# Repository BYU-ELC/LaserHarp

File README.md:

# LaserHarp
Contains code and project files for the Laser Harp project

The Laser harp project accepts inputs from the laser sensors/beams. When a laser beam is interrupted, the consequent signal will be converted into a musical/audio output corresponding with the 'string' played. As such, this functions generally as a classical harp, simply implementing the lasers to operate as harp strings.

Currently the project is controlled by a teensy with an audio shield. The 5 volt power source is stepped down to 3.3 volts to power 8 always on lasers which are pointed at photodiodes. The photodiodes each have a simple BJT circuit to amplify their output which is detected by the teensy. The audio shield on the teensy generates a tone every time a laser beam is interrupted.

The original board schematic is handwritten in LaserHarpSchematic.pdf, but the new schematics and layouts are in the Laser Harp PCB.sch and Laser Harp PCB.brd files respectively. You should use these for future development or repair.

 --

FUTURE DEVELOPMENT:

Currently the Laser Harp is using a PCB we milled out here in the shop which is nice, but it might be nice to order a professional one. Also, it is Revision 2, meaning I had to manually change the connection from pin 7 to pin 8 (See schematic commit notes).

If the Photo Diode boards are ever replaced, you should add an additional pad to the board to make it easier to connect the power supply since it runs from one board to the next.

It might be nicer to have the buttons attached to the Laser Harp PCB instead of on a separate board, or at least mounted on the base of the Laser Harp more professionally.

The fog currently works, but it could be improved by replacing the fans on the reservoir with stronger fans and possibly redoing the tubing to get better fog distribution.

If someone can find a library of actual harp audio files (instead of piano), that would be awesome. Just make sure to format the files as described the in the Laser Harp Hardware Documentation.

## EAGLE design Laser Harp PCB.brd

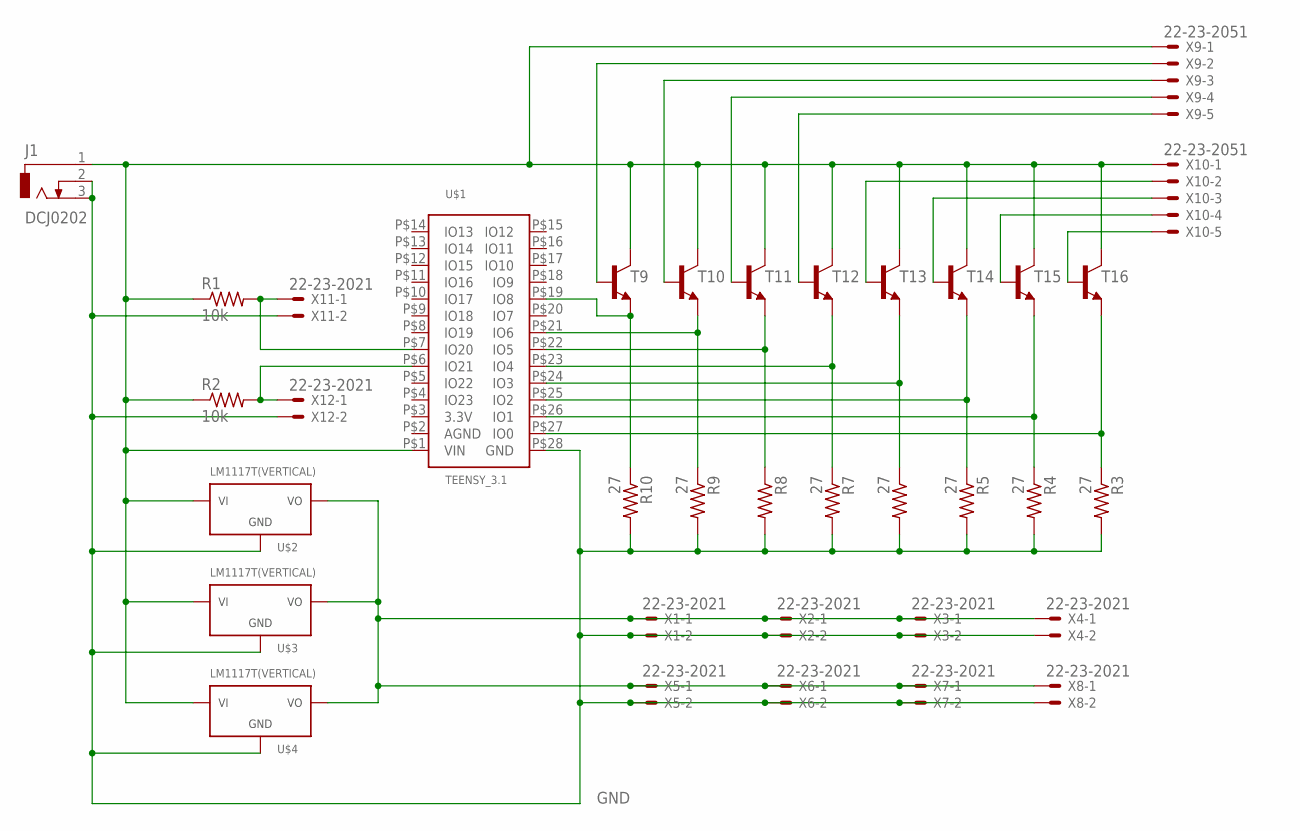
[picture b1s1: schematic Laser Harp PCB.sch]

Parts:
J1: DCJ0202
R1, R2: 10k; 0207/7
R3, R4, R5, R6, R7, R8, R9, R10: 27; 0207/7
T9, T10, T11, T12, T13, T14, T15, T16: 2N3904-NPN-TO92-EBC; TO92-EBC
U$1: TEENSY_3.1
U$2, U$3, U$4: LM1117T(VERTICAL); 317TS
X1, X2, X3, X4, X5, X6, X7, X8, X11, X12: 22-23-2021
X9, X10: 22-23-2051

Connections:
GND: J1.2, J1.3, R3.2, R4.2, R5.2, R6.2, R7.2, R8.2, R9.2, R10.2, U$1.P$28 (GND), U$2.1 (GND), U$3.1 (GND), U$4.1 (GND), X1.2, X2.2, X3.2, X4.2, X5.2, X6.2, X7.2, X8.2, X11.2, X12.2
unnamed: U$2.2 (VOUT), U$3.2 (VOUT), U$4.2 (VOUT), X1.1, X2.1, X3.1, X4.1, X5.1, X6.1, X7.1, X8.1
unnamed: J1.1, R1.1, R2.1, T9.C, T10.C, T11.C, T12.C, T13.C, T14.C, T15.C, T16.C, U$1.P$1 (VIN), U$2.3 (VIN), U$3.3 (VIN), U$4.3 (VIN), X9.1, X10.1
unnamed: R3.1, T16.E, U$1.P$27 (IO0)
unnamed: R4.1, T15.E, U$1.P$26 (IO1)
unnamed: R5.1, T14.E, U$1.P$25 (IO2)
unnamed: R6.1, T13.E, U$1.P$24 (IO3)
unnamed: R7.1, T12.E, U$1.P$23 (IO4)
unnamed: R8.1, T11.E, U$1.P$22 (IO5)
unnamed: R9.1, T10.E, U$1.P$21 (IO6)
unnamed: R2.2, U$1.P$6 (IO21), X12.1
unnamed: R1.2, U$1.P$7 (IO20), X11.1
unnamed: R10.1, T9.E, U$1.P$19 (IO8)
unnamed: T9.B, X9.2
unnamed: T10.B, X9.3
unnamed: T11.B, X9.4
unnamed: T12.B, X9.5
unnamed: T13.B, X10.2
unnamed: T14.B, X10.3
unnamed: T15.B, X10.4
unnamed: T16.B, X10.5

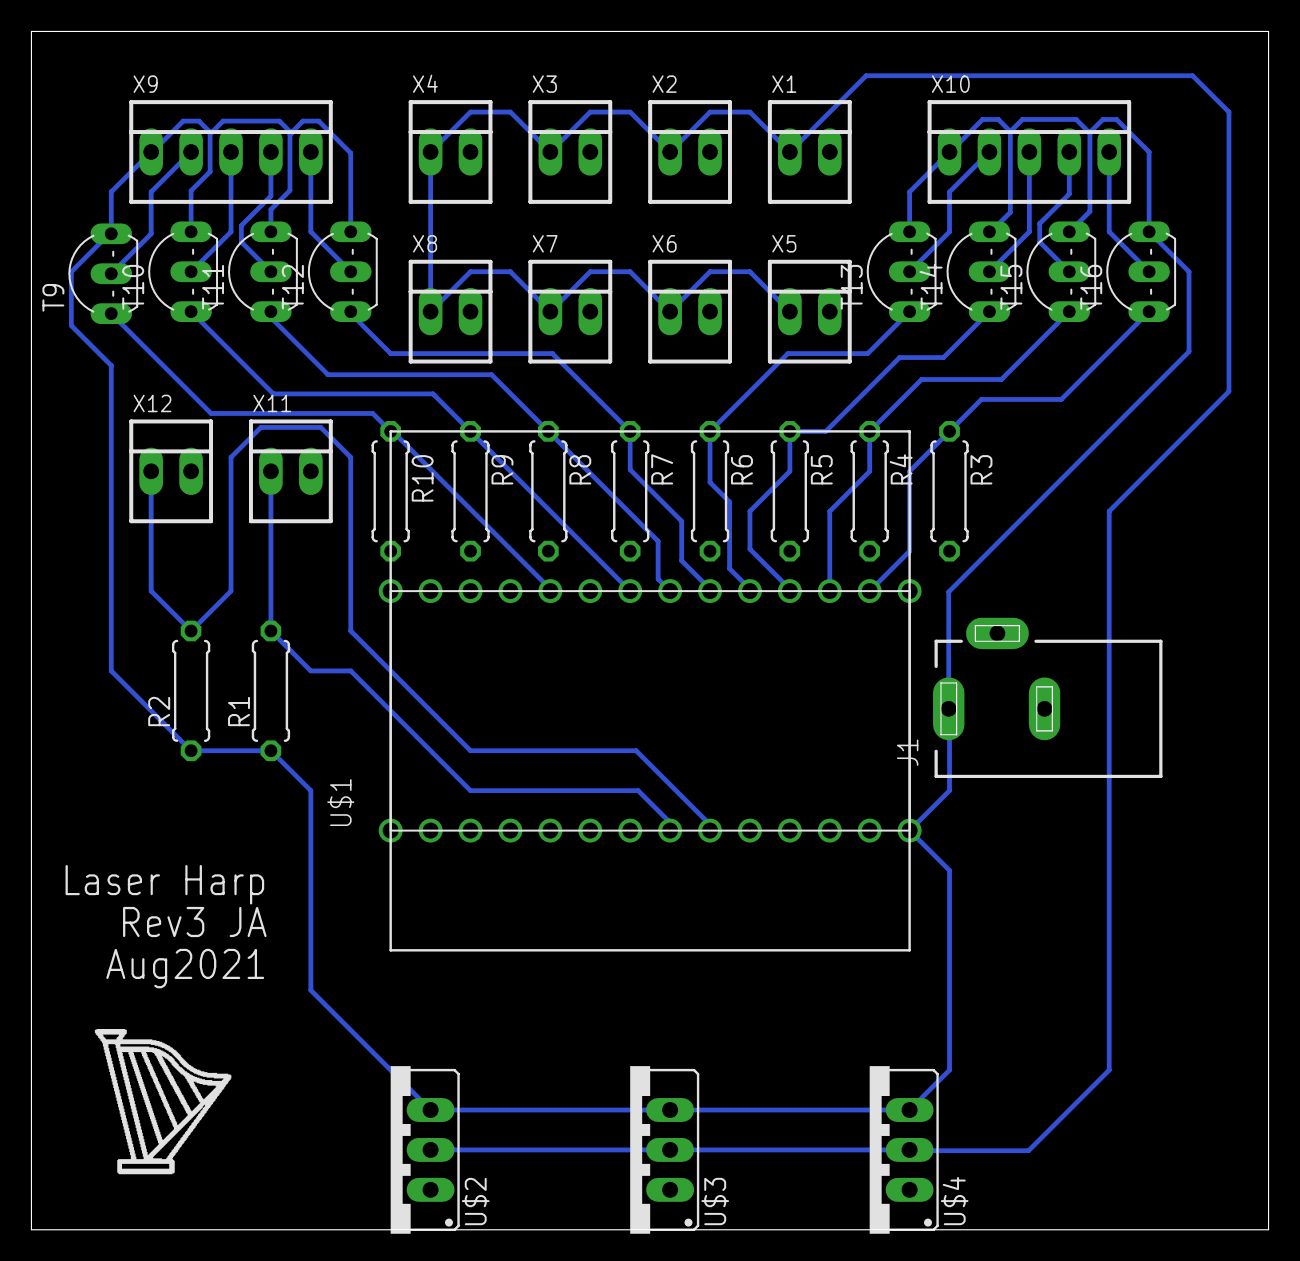
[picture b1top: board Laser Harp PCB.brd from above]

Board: 2 copper layers, 78.7 x 76.3 mm, 35 parts (0 on the bottom side), 21 nets.

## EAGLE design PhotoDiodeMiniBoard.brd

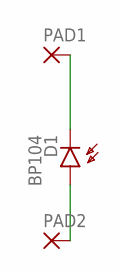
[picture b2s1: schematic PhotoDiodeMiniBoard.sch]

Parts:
D1: BP104
PAD1, PAD2: 2,15/1,0

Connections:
unnamed: D1.K (C), PAD1.1
unnamed: D1.A, PAD2.1

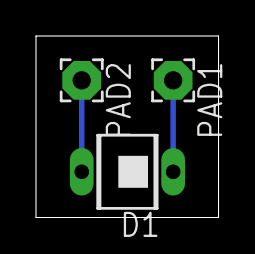
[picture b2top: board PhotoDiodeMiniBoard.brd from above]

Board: 2 copper layers, 10.1 x 10.1 mm, 3 parts (0 on the bottom side), 2 nets.

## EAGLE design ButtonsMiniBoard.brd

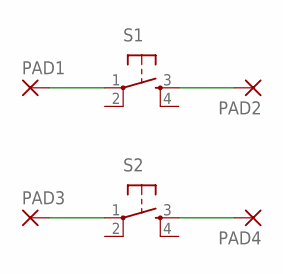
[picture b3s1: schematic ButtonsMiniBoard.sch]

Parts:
PAD1, PAD2, PAD3, PAD4: 2,15/1,0
S1, S2: TAC_SWITCHPTH; TACTILE-PTH

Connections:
unnamed: PAD1.1, S1.1
unnamed: PAD2.1, S1.3
unnamed: PAD3.1, S2.1
unnamed: PAD4.1, S2.3

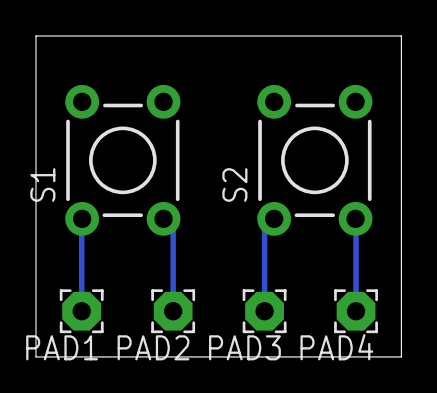
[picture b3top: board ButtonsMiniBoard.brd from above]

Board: 2 copper layers, 20.3 x 17.8 mm, 6 parts (0 on the bottom side), 4 nets.

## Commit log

2021-05-19 Add hand written schematic
2021-05-19 Add some specific description of the project
2021-05-26 Create Teensy Audio Test Code
    This is test code used to verify the functionality of the Teensy 3.1, the Audio Adapter Board Rev B, and the SD card. All are working, and the program successfully reads and plays the wav files on th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
2021-07-21 Create Basic Functionality Code
    Allows the harp to play one note at a time, C5-C6 major scale.
    The commented out code includes functions to play two or three notes at a time. 4+ notes does not play properly.
2021-08-24 Update Basic Functionality Code
    Updated pin numbers based on the new PCB layout
2021-08-26 Schematics and Board Layouts
    Schematics and Board Layouts for the main PCB, the buttons board, and the photodiode board. These are for the working revision used at NSO. Further revision may improve the design.
2021-08-26 Updated Documentation
2021-08-27 Create Improved Code
    This code contains improvements like allowing the user to play multiple notes simultaneously (up to 3, the teensy doesn't handle more than 3 well), shifting the range of the notes, switching between 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
    One button shifts down a half step, the other shifts up a half step. The high and low notes loop around when you reach the extremes. Pressing both buttons together changes between a major and minor s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
2021-09-14 Updated pin connection
    The BJTs used to connect to pins 0 through 7 of the Teensy, but the Audio Shield uses pin 7 to transmit information from the micro sd card to the Teensy. I changed the connection from pin 7 to pin 8.
2021-09-14 Update pin connections
    The BJTs used to connect to pins 0 through 7 of the Teensy, but the Audio Shield uses pin 7 to transmit information from the micro sd card to the Teensy. I changed the connection from pin 7 to pin 8.
2021-09-14 Added future development section
2021-09-14 Rename Teensy Audio Test Code to Code - Teensy Audio Test
2021-09-14 Rename Basic Functionality Code to Code - Basic Functionality
2021-09-14 Rename Improved Code to Code - Improved Functionality
